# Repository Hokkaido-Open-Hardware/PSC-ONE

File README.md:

<p align="center">
  
</p>

# PSC-ONE SoC

[日本語・開発の目的](README_JP.md) · [Documentation](docs/README.md)

### Technical Specifications (PDF)

- **[PSC-ONE SoC Specification (Rev.0.9)](./docs/specs/PSC-ONE_SpecSheet.pdf)**  
  CPU, MMU, cache, SDRAM, NPU, peripherals, and SoC architecture.

- **[PSC-OS Specification (Rev.0.9)](./docs/specs/PSC_OS_Specs.pdf)**  
  OS architecture, boot process, system calls, ELF loader, FAT32, MicroPython, and TFLite runtime.

------------------------------------------------------------------------

An open-source full-stack RISC-V SoC platform for FPGA-based edge computing and AI acceleration.  
PSC-ONE integrates a custom CPU, memory subsystem, peripherals,
operating system, and AI accelerator into a unified architecture,
enabling end-to-end hardware/software co-design.

The PSC-NPU (SynapEngine) accelerator is controlled directly through custom
RISC-V CSR registers and accesses matrix data through the shared
cache/memory subsystem. This reduces explicit data transfers and
redundant memory copies during matrix operations and future neural-network workloads.

## Introduction Video

------------------------------------------------------------------------

## Contents

<!-- contents -->
- [What is PSC-ONE?](#what-is-psc-one)
- [PSC-ONE SoC Architecture](#psc-one-soc-architecture)
- [Repository Structure](#repository-structure)
- [Hardware Components](#hardware-components)
- [Software Stack](#software-stack)
- [CPU (PSC_RV32)](#cpu-psc_rv32)
- [CPU (PSC_RV32_V1)](#cpu-psc_rv32_v1)
- [CPU (PSC_RV32_V2)](#cpu-psc_rv32_v2)
- [CoreMark (CPU Core Only)](#coremark-cpu-core-only)
- [PSC-ONE AI](#psc-one-ai)
- [PSC-OS](#psc-os)
- [Demo](#demo)
- [PSC-ONE Speech Recognition Project](#psc-one-speech-recognition-project)
- [FST Viewer](#fst-viewer)
- [Development Status](#development-status)
- [Future Work](#future-work)
- [Getting Started](#getting-started)
- [Repository Status](#repository-status)
- [License](#license)
<!-- /contents -->

------------------------------------------------------------------------

The current PSC-ONE prototype hardware.\

The displayed color bars are generated directly by the PSC-ONE hardware and confirm correct operation of the LCD subsystem.

The PSC-ONE boot logo rendered on the actual FPGA hardware during system startup, demonstrating successful LCD initialization and graphics output.\

## What is PSC-ONE?

PSC-ONE is an open-source full-stack RISC-V SoC project developed by QPSC-Design.

It aims to build a fully custom edge computing platform from the ground up, including the following components:

- A custom RV32-based RISC-V CPU core
- A memory subsystem, including an SDRAM controller, caches, and an Sv32 MMU
- An SD card boot and storage interface
- Memory-mapped peripheral interfaces
- An AI acceleration engine, PSC-NPU, based on a systolic array architecture
- A custom operating system, PSC-OS

PSC-ONE is not just a CPU core, but a complete experimental SoC platform for research, edge AI development, and architectural exploration.

------------------------------------------------------------------------

## PSC-ONE SoC Architecture

This section presents the overall PSC-ONE SoC architecture, including the
PSC_RV32 CPU, memory subsystem, peripherals, PSC-OS, and PSC-ONE AI.

------------------------------------------------------------------------

## Repository Structure

| Directory | Contents |
| --- | --- |
| [hardware](hardware/README.md) | CPU/SoC RTL, bootloader and simulation |
| [software](software/os/OVERVIEW.md) | PSC-OS, MicroPython and applications |
| [board](board/README.md) | Board designs and prototype setup |
| [docs](docs/README.md) | Specifications, guides and validation records |
| [FST Viewer](tool/FST_viewer/README.md) | CPU waveform viewer |
| [IP](ip/README.md) | Project IP notes |

CPU v1 supports two PULP/CORE-V dot-product instructions. See the
[PULP specification](docs/cpu_pulp.md) ([日本語](docs/cpu_pulp_JP.md)).

------------------------------------------------------------------------

## Hardware Components

The hardware side of PSC-ONE currently includes:

- `PSC_RV32` custom RISC-V CPU core
- SDRAM controller
- SD card interface (SPI mode)
- Memory-mapped peripheral system
- PSC-NPU (SynapEngine) AI accelerator

------------------------------------------------------------------------

## Software Stack

The software side of PSC-ONE currently includes:

- `PSC-OS`, a custom operating system for the platform
- Boot and initialization flow for FPGA-based execution
- User programs and runtime experiments, including UART-based output demos

------------------------------------------------------------------------

## CPU (PSC_RV32)

### CPU Architecture

`cpu_legacy` is the CPU core developed during the initial prototyping phase of PSC-ONE.

See the [CPU guide](docs/cpu.md) and [hardware overview](hardware/README.md).

------------------------------------------------------------------------

## CPU (PSC_RV32_V1)

### CPU Architecture

> Diagram note: the drawing labels the main instruction FIFO as 32 words.
> The current v1 FetchUnit defaults to 16 words; the predicted-target FIFO
> remains 8 words. The image is retained as an earlier configuration.

See the [CPU guide](docs/cpu.md) and [hardware overview](hardware/README.md).

------------------------------------------------------------------------

## CPU (PSC_RV32_V2)

### Experimental Out-of-Order Architecture

`PSC_RV32_V2` is an experimental CPU with register renaming, a reorder buffer
(ROB), and an instruction queue (IQ). The current defaults are two ROB entries,
two IQ entries, and 34 physical registers. Independent ready instructions can
execute ahead of older stalled instructions; architectural state retires in
program order. These two in-flight slots do not imply two instructions retire
per clock. See the [hardware overview](hardware/README.md) for implementation links.

See the [CPU guide](docs/cpu.md) and [hardware overview](hardware/README.md).

------------------------------------------------------------------------

## CPU RV64 architecture

PSC_RV64 is an experimental 64-bit extension of the PSC_RV32 design.

targets RV64IM with Zicsr and Zifencei, extending the integer registers and
datapath to 64 bits while retaining 32-bit instruction encodings.

RV64 adds 64-bit load/store operations and word operations that produce
32-bit results sign-extended to 64 bits. The port also requires RV64-specific
handling of shift amounts, arithmetic, multiplication and division.

Initial development focuses on bare-metal execution and adapting the existing
C/C++ test programs using `-march=rv64im_zicsr_zifencei -mabi=lp64`.
Sv39 virtual memory and PSC-OS support are separate development steps;
64-bit execution alone does not establish Linux compatibility.

The core remains experimental. RV32 regression results and CoreMark scores
do not establish RV64 correctness or performance; RV64 validation results
will be documented separately.

------------------------------------------------------------------------

## CoreMark (CPU Core Only)

CoreMark was also measured with the SDRAM/cache path removed and replaced by a 1-cycle cocotb memory model.
This isolates the CPU core from SDRAM wait states, cache misses, and refill latency.

```text
CPU       CoreMark    CoreMark/MHz    Execution Time    CRC Validation
-----------------------------------------------------------------------
cpu_v1    80.879974   0.808800        12.364 s          PASS
cpu_v2    53.287861   0.532879        18.766 s          PASS
```

Recorded measurement conditions (historical results, not rerun for this documentation update):

- 100 MHz
- GCC 14.2.0
- The original table states 500 iterations for both CPUs; this is inconsistent with the v1 score/time pair (see note below).
- 1-cycle memory response
- No SDRAM wait states
- No cache-miss or refill penalty
- Identical CoreMark binary for `cpu_v1` and `cpu_v2`
- CRC Validation: PASS

These are CPU-core-only measurements under a 1-cycle memory model.
The v1 score × execution time is approximately 1,000, whereas v2 gives 500.
The original v1 iteration count or score/time entry therefore needs confirmation
from its measurement log. Values are retained as recorded, not silently corrected.
See [CoreMark reproduction and interpretation](hardware/sim/coremark_psc/README.md).

------------------------------------------------------------------------

## PSC-ONE AI

PSC-ONE AI is a hardware accelerator platform for matrix multiplication (GEMM),
built around a custom systolic-array architecture.

It is part of the broader PSC-ONE experimental SoC platform,
which integrates:

- Custom RISC-V CPU
- Memory subsystem
- AI accelerator
- Hardware/software co-design environment

The project focuses on exploring efficient dataflow architectures
under constrained memory bandwidth for edge AI systems.

------------------------------------------------------------------------

### PSC-ONE AI Architecture

> Diagram note: “share a single multiplier” describes the shared-arithmetic
> concept. The legacy multiplier count is configurable; NPU v1 uses four
> physical multiplier lanes. The drawing is not an exact v1/v2 netlist.

The system integrates the PSC-NPU systolic array
with the PSC-ONE SoC platform.

------------------------------------------------------------------------

### PSC-ONE AI Features

- 4×4 INT8 systolic array
- Output-Stationary (OS) dataflow
- Direct control through custom RISC-V CSR registers
- Direct matrix data access through the CPU cache/memory subsystem
- Integrated with the custom PSC-RV32 processor
- Experimental hardware/software co-design platform

------------------------------------------------------------------------

### 8×8 Matrix Multiplication Performance

The following historical results compare the execution time of an 8×8 matrix multiplication across different PSC-RV32 configurations and the systolic array accelerator.

#### Execution Time Comparison

| Configuration                                  | Execution Time | Performance vs. V1 |
| ---------------------------------------------- | -------------: | -----------------: |
| PSC_RV32                                       |         591 µs |       ~1.80× faster |
| PSC_RV32_V1                                    |        1066 µs |           Baseline |
| Systolic Array                                 |          44 µs |       ~24.2× faster |
| PSC_RV32_V1 (Fetch FIFO enabled)               |         742 µs |       ~1.44× faster |
| PSC_RV32_V1 (R/I-Type pipeline enabled)        |         651 µs |       ~1.64× faster |

#### Results

The systolic array completed the 8×8 matrix multiplication in **44 µs**, approximately **24.2× faster** than the baseline PSC_RV32_V1 processor.

Enabling the Fetch FIFO reduced the PSC_RV32_V1 execution time from **1066 µs to 742 µs**. Enabling the R/I-Type pipeline further reduced it to **651 µs**, approaching the performance of the original PSC_RV32 processor at **591 µs**.

These results demonstrate that both instruction-fetch optimization and R/I-Type pipelining significantly improve CPU performance. However, the dedicated systolic array still provides a much larger performance advantage for matrix multiplication workloads.

------------------------------------------------------------------------

### PSC-NPU and PicoRV32 Resource Scale Comparison

PicoRV32 is an archived generic-cell result; its MUX count is corrected to 100
from the saved log. FF-family counts are register cells, not individual bits.
See the [CPU comparison and provenance](docs/cpu.md#psc_rv32-vs-picorv32-yosys-analysis).

#### Resource Comparison

This is a historical generic Yosys cell comparison for the legacy NPU, not
FPGA LUT/FF usage or the current NPU v1 resource count. NPU v1 has four physical
multiplier lanes; see [its implementation](hardware/rtl/soc/npu_v1/README.md).

| Metric         | PSC-NPU (4×4)        | PicoRV32 |
| -------------- | -------------------: | -------: |
| Cells          |                  555 |      515 |
| Multipliers    |                **2** |    **0** |
| Adders         |                   25 |        8 |
| Multiplexers   |                  113 |      100 |
| FF-family cells |                   88 |      105 |
| Control Logic  |             Moderate |     High |

> Multiplexer counts include Yosys `$mux` cells only and exclude `$pmux` cells.

- A **dataflow-oriented compute engine (Systolic Array)**
- A **control-oriented general-purpose CPU (PicoRV32)**

------------------------------------------------------------------------

## PSC-OS

[OS architecture and boot](docs/psc_os.md) · [API reference](docs/psc_os_api.md) · [MMU](docs/cpu_mmu.md)

PSC-OS is a custom operating system developed specifically for the PSC-ONE platform.

Unlike Linux, BSD, or existing RTOSes, PSC-OS is designed together with the PSC_RV32 CPU, memory subsystem, peripherals, and hardware accelerators, providing a tightly integrated hardware/software co-design environment.

The following diagram illustrates the software architecture of PSC-OS, including user applications, the kernel, device drivers, and the underlying PSC-ONE hardware platform.

> Diagram note: FAT32 is drawn inside the kernel, but the current shell/ELF path
> links FAT32 into the user image and accesses SD hardware through system calls.
> The image is retained as a conceptual overview, not a privilege-boundary map.

> This diagram presents the conceptual architecture of PSC-OS and PSC-ONE. Some modules shown may represent planned or experimental extensions.

Current PSC-OS features include:

- Bootloader and kernel
- Machine, Supervisor, and User privilege modes
- Sv32 virtual memory
- ECALL-based system-call interface
- Interactive command shell
- FAT32 filesystem support
- SD-card boot and storage
- User-program loading and execution
- Device drivers for UART, LCD, I2S microphone, and SD card
- PSC-NPU software support; PFE OS API integration remains future work

PSC-OS serves both as the runtime environment for the PSC-ONE SoC and as an experimental platform for operating-system, CPU, and hardware/software co-design research.

------------------------------------------------------------------------

### ELF Loader

PSC-OS includes an ELF loader for running RISC-V user programs from the SD card. The loader reads an ELF executable through the FAT32 filesystem, places its loadable segments in memory, and starts execution at the entry point specified by the file.
This allows user applications to be built as ELF executables instead of being converted to raw memory images. It also provides a foundation for expanding PSC-OS’s user-program support.

Example of running the sample `HELLO.ELF` from the PSC-OS shell:

```text
PSC_OS> run HELLO.ELF
ELF: entry=00400000 sp=00500000 pages=3
Hello from user ELF!
run: exit 0
PSC_OS>
```

------------------------------------------------------------------------

### MicroPython on PSC-OS

MicroPython has been ported to PSC-OS and can run as a user-space application on the custom PSC_RV32 CPU.
The following console output is an excerpt from an actual execution on PSC-ONE.

```text
PSC_OS Boot Start.........
--- memset done ---
Test Ver: test_1.5.0

+--------------------------------------------------+
|                    PSC_OS                        |
|            Minimal RISC-V Kernel Boot            |
+--------------------------------------------------+
| CPU   : RV32 (Supervisor mode)
| MMU   : SV32
| UART  : SBI console or
| UART  : MMIO console
| CMD   : hello, primes, dump
| CMD   : sa_start
| CMD   : sd_read, sd_write
| CMD   : mic_read, mic_write
| CMD   : fat32_info, fat32_ls, fat32_cat
| CMD   : fat32_touch
| CMD   : speech
+--------------------------------------------------+
...
MicroPython v1.29.0-preview.727.g7de32aa1ae on 2026-08-18; minimal with unknown-cpu

>>> a = 10
>>> a * 20
200

>>> p = [n for n in range(10)]
>>> print(p)
[0, 1, 2, 3, 4, 5, 6, 7, 8, 9]

>>> print(sum(p))
45

>>> print(sum(((i%1000)*(i%1000)//((i%97)+1) for i in range(1,5000))))
88859578

>>> import math
>>> print(sum(math.sin(i) for i in range(100)))
0.37919468

>>> [print(" "*int(20+15*math.sin(i/4))+"*") for i in range(40)]
                    *
                       *
                           *
                              *
                                *
                                  *
                                  *
                                 *
                               *
                            *
                         *
                      *
                  *
              *
           *
        *
      *
     *
       *
         *
            *
               *
                   *
                       *
                          *
                             *
                                *
                                  *
                                 *
                               *
                             *
                          *
                      *
                  *
               *

>>> import psc

>>> psc.run("TEST1.PY")

Hello from SD card

10

20

2000

>>> psc.run("TEST2.PY")

=== PSC-ONE MicroPython SD Test ===

1 sin= 0.32719472 cos= 0.9800666 mix= 0.32067264

2 sin= 0.6183698 cos= 0.921061 mix= 0.5695563

3 sin= 0.841471 cos= 0.8253356 mix= 0.694496

4 sin= 0.9719379 cos= 0.6967067 mix= 0.6771557

5 sin= 0.99540792 cos= 0.5403023 mix= 0.5378212

```

This demonstrates that the PSC-ONE software stack can execute an interactive Python environment directly on the custom RISC-V processor, including integer arithmetic, list comprehensions, generators, and floating-point math functions provided by MicroPython.

------------------------------------------------------------------------

### Thonny on MicroPython

Thonny provides a graphical development environment for working with MicroPython on PSC-OS. It connects to PSC-ONE through a USB-to-UART interface, allowing Python code to be edited on the PC and sent to the board for execution.

The integration uses MicroPython’s raw REPL protocol to transfer code and return execution results. The code runs on the custom PSC_RV32 CPU, while Thonny displays program output and error messages on the PC.

With the PSC-OS Thonny support in place, the basic workflow is:

1. Start MicroPython from the PSC-OS shell using the `microPython` command.
2. Close the serial terminal to release the UART port.
3. Select **MicroPython (generic)** in Thonny and choose the serial port connected to PSC-ONE.
4. Write a Python script in the editor and run it on the board.

Scripts can be transferred and executed directly in RAM without first saving them to the SD card. Access to PSC-ONE-specific functions is provided through the `psc` module.

This integration brings the existing MicroPython environment into a desktop editor, making it easier to develop and test Python programs for PSC-ONE.

------------------------------------------------------------------------

## Demo

### PSC-OS LCD Demo

This video shows a live demonstration of the PSC system running on FPGA hardware.\
It highlights real-time interaction between the CPU, SD card interface, and UART output.\
The system successfully boots and executes software on a fully integrated hardware platform.

------------------------------------------------------------------------

## PSC-ONE Speech Recognition Project

### Background

This speech-recognition project started from PSC-ONE.

In June 2026, I wrote **"PSC-ONEによる音声認識①（キックオフ編）"**.

About two months have passed since then.

The project has finally reached an important milestone, so the current
results are summarized here.

### Image

The PC is connected to the PSC-ONE board via UART.
Speech recognition is performed by speaking into the microphone connected to PSC-ONE,
while the recognition results are displayed on the PC through the UART console.\

### Equipment

-   PSC-ONE FPGA platform
-   Custom PSC_RV32 RISC-V CPU
-   PSC-OS
-   I2S microphone
-   PSC-NPU (SynapEngine) AI accelerator

### Results

The following output is from an actual speech-recognition test running
on PSC-ONE.

#### UP

``` text
PSC_OS> speech
Speech recognition start

（私の声でアップ）

SPEECH RECORD START samples=48000
SPEECH RECORD END samples=48000
VOICE RANGE start=0 end=32000
SCORE UP=22776 DOWN=-71191 UNKNOWN=-14509
SPEECH RESULT=UP
RESULT: UP
```

#### DOWN

``` text
PSC_OS> speech
Speech recognition start

（私の声でダウン）

SPEECH RECORD START samples=48000
SPEECH RECORD END samples=48000
VOICE RANGE start=0 end=32000
SCORE UP=-85630 DOWN=5339 UNKNOWN=-9757
SPEECH RESULT=DOWN
```

In the current implementation, speech recognition succeeds approximately
**70% of the time**.

This marks the completion of the first working PSC-ONE
speech-recognition implementation.

------------------------------------------------------------------------

## PSC-ONE YOLOv8n Demo Project

This project demonstrates YOLOv8n object detection on **PSC-ONE**, a custom FPGA-based RISC-V SoC.

JPEG images and a TFLite model are loaded from an SD card. PSC-OS handles image preprocessing, inference, and detection postprocessing. The project explores running neural-network inference on a small FPGA system using a variety of test images.

### System Configuration

- **Hardware:** Tang Nano 20K / PSC-ONE
- **CPU:** Custom RISC-V CPU
- **OS:** PSC-OS
- **Model:** YOLOv8n, INT8-quantized TFLite model (approximately 3.5 MB)
- **Model input resolution:** 160 × 160 pixels
- **Image source:** JPEG files stored on an SD card

### Input Images and Detection Results

| Sample | Input Image | Detection Result |
| :--- | :---: | :---: |
| ANIME |  |  |
| BUS |  |  |
| CUPBAN |  |  |
| NEKO |  |  |
| DOG |  |  |

This demo focuses on validating inference in an embedded environment rather than achieving real-time performance. Detection results depend on the input image and the object classes supported by the pretrained model.

------------------------------------------------------------------------

## FST Viewer

PSC-ONE includes **FST Viewer (PSC_RV32 Trace Studio)**, a Python-based browser GUI for visualizing CPU execution traces generated by simulation.

The viewer reads FST/VCD waveform files and presents CPU activity at the instruction and architectural level rather than displaying only raw RTL signals. It is designed specifically for the PSC_RV32 processor family and does not require any modification to the RTL.

Currently supported CPU architectures are:

- `PSC_RV32` (legacy FSM architecture)
- `PSC_RV32_V1` (valid/ready pipeline architecture)
- `PSC_RV32_V2` (experimental out-of-order architecture)

The CPU architecture is automatically detected from the trace structure.

FST Viewer provides:

- Instruction-level execution timeline
- CPU pipeline and execution-stage visualization
- Instruction tracking across multiple cycles
- PC and instruction search
- Instruction filtering
- Instruction Ledger with PC, instruction word, disassembly, execution cycles, and retire status
- Cycle Inspector for register operands, execution results, memory accesses, hazards, and CPU state
- Architectural register display (`x0`–`x31`) with ABI names and value-change highlighting
- MUL/DIV execution and wait-state visualization
- Support for legacy, V1, and experimental V2 CPU architectures

The horizontal axis represents CPU clock cycles, allowing execution behavior to be inspected cycle by cycle.

For example, the viewer can show how an instruction moves through the CPU, how long it remains in each execution stage, when register values change, and where pipeline stalls or long-latency MUL/DIV operations occur.

The viewer runs locally using Python and a standard JavaScript/Canvas-capable web browser.

```bash
cd PSC-ONE/tool/FST_viewer
python3 fst_viewer.py
```

When no trace file is specified, the viewer automatically selects the latest FST/VCD file generated in:

```text
hardware/sim/wave/
```

A specific trace can also be opened directly:

```bash
python3 fst_viewer.py trace.fst
```

The default web interface runs on `127.0.0.1:8000`. If the port is already in use, the viewer automatically searches for the next available port.

FST Viewer is intended to make PSC_RV32 CPU development and verification easier by providing a higher-level view of processor execution than conventional waveform inspection alone.

------------------------------------------------------------------------

## Development Status

### Hardware

#### CPU
- [x] RV32I Base Integer Instruction Set
- [x] RV32M Multiply/Divide Extension
- [x] Zicsr and Zifencei Extensions
- [x] Selected PULP SIMD instructions (`cv.dotup.h`, `cv.dotsp.b`)
- [ ] Full Pipeline Execution
- [x] Partial Pipeline Execution for selected instruction types
- [x] Branch Instructions
- [x] Load / Store Instructions
- [x] CSR Support
- [x] ECALL / SRET Support
- [x] MMU (Sv32)
- [x] Interrupt Controller

#### Memory System
- [x] SDRAM Controller
- [x] AXI4 Memory Interface
- [x] Cache Controller
- [x] Virtual Memory Support
- [x] DMA Engine

#### AI Accelerator
- [x] PSC-NPU Architecture
- [x] 4×4 INT8 Systolic Array
- [x] Matrix Multiplication API
- [x] Shared Memory Integration
- [ ] Larger Systolic Array
- [ ] Quantized Neural Network Inference

#### Peripherals
- [x] UART
- [x] LED Controller
- [x] Timer
- [x] SD Card (SPI Mode, Read)
- [x] SD Card (SPI Mode, Write)
- [x] LCD Controller
- [ ] Ethernet
- [ ] USB

### Software

#### PSC-OS
- [x] Bootloader
- [x] FAT32 Bootloader
- [x] Kernel
- [x] User Mode Execution
- [x] System Call Interface
- [x] Command Shell
- [x] Memory Management
- [x] SD Card Driver
- [x] SD Card Program Loader
- [x] FAT32 File System
- [x] ELF Loader
- [ ] Networking Stack

#### Device Drivers
- [x] UART
- [x] Timer
- [x] SDRAM Controller
- [x] LCD Controller (ILI9488)
- [x] I2S Microphone Interface
- [x] Systolic Array Accelerator

#### Applications
- [x] Prime Number Benchmark
- [x] Matrix Multiplication Demo
- [x] SDRAM Test
- [x] SD Card Test
- [x] FAT32 File Browser (`ls`, `cat`)
- [x] FAT32 File Write
- [x] JPEG Image Viewer (jpeg) — 480×320 LCD Display
- [x] AI Inference Demo
- [x] Audio Processing Demo
- [x] Speech Recognition Demo

### Verification

#### Simulation
- [x] Icarus Verilog
- [x] Verilator
- [x] Cocotb Test Environment
- [x] Official RISC-V ISA tests: 49 RV32I/RV32M tests passed
- [x] SDRAM Tests
- [x] MMU Tests
- [x] PSC-OS Boot Test

#### FPGA
- [x] Tang 20K
- [x] SDRAM Boot
- [x] PSC-OS Boot
- [x] UART Console
- [x] SD Card Boot
- [x] PSC-NPU Execution
- [ ] Long-Term Stability Test

### Documentation

- [x] Project Overview
- [x] Build Instructions
- [x] Simulation Guide
- [x] Hardware Architecture
- [ ] Software Architecture
- [ ] Developer Guide
- [x] API Reference

### Future Goals

- [ ] PSC-ONE v1.0 Release
- [ ] Neural Network Inference on PSC-NPU
- [ ] Extend the existing speech-recognition demo
- [ ] Self-Balancing Robot Demo
- [ ] Custom ASIC Prototype

------------------------------------------------------------------------

## Future Work

### Demonstration Robot

A demonstration of a two-wheeled self-balancing robot controlled by the PSC-ONE board is also planned

### PFE

#### PSC-ONE Phase Flow Engine

The PSC-ONE Phase Flow Engine is an experimental hardware accelerator architecture developed as part of the PSC project.
It is designed for future AI, signal-processing, and data-flow computing research on the PSC-ONE platform.

Location:

```text
hardware/rtl/soc/pfe/
```

------------------------------------------------------------------------

## Getting Started

Commands below start at the repository root (the directory containing `PSC-ONE/`).
With the RISC-V toolchain, Verilator and a Python environment containing cocotb:

```sh
cd PSC-ONE/hardware/sim
make -f Makefile.riscv.sim simulate_RISCV_TESTS_PARALLEL CPU_VERSION=v1
make -f Makefile.cpu.core simulate_CPU_CORE CPU_VERSION=v1
make -f Makefile.pscos simulate_PSCOS CPU_VERSION=v1
```

OS simulation can take a long time. See the [software guide](software/os/OVERVIEW.md)
and [board setup](board/PSC-ONE/README.md) for the next steps.

At a high level, the workflow is as follows:

1. Build the hardware design
2. Program the FPGA
3. Prepare the boot image or software binaries
4. Run the system and observe output through the available interfaces

For detailed instructions, see the [Getting Started Guide](docs/getting-started.md).

------------------------------------------------------------------------

## Repository Status

This repository is an experimental research project
and is under active development.

RTL, software, and architecture may change frequently.

------------------------------------------------------------------------

## License

MIT License

------------------------------------------------------------------------

### Work in Progress

This project is actively under development.\
Features, architecture, interfaces, and documentation may change as the design evolves.

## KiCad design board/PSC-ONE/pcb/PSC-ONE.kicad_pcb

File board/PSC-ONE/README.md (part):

# PSC-ONE Design

[PSC-ONE](../../README.md) · [Documentation](../../docs/README.md)

The current PSC-ONE prototype hardware.\

<!-- contents -->
- [Purpose](#purpose)
- [Features](#features)
- [Getting Started](#getting-started)
- [License](#license)
<!-- /contents -->

## Purpose

PSC-ONE is a hardware evaluation and demonstration platform for the PSC project.

The board is designed to verify and validate the functionality of the PSC CPU, operating system, memory subsystem, peripherals, and AI acceleration technologies in a real hardware environment.

It also serves as a demonstration platform for various embedded applications, including:

- Voice recognition
- AI inference
- Graphics and display control
- Sensor integration
- Real-time embedded systems

## Features

- Custom PSC RISC-V CPU
- PSC-OS operating system support
- SDRAM memory interface
- LCD display interface
- Optional touch panel support
- SD card storage interface
- UART debugging console
- GPIO expansion
- AI accelerator integration support

## Getting Started

### Program the FPGA

Build the FPGA bitstream and program the PSC-ONE board using the Gowin Programmer.

After successful programming, connect:

* UART console
* SD card containing PSC-OS images
* LCD module (optional)

### Prepare the SD Card

Match the SD layout to the bootloader in the FPGA image. Two flows exist:

| Bootloader | SD layout |
| --- | --- |
| [FAT32 loader](../../software/os/src/boot/bootloader_fat32.c) | `KERNEL.MEM` and `USER.MEM` in the FAT32 root |
| [Legacy raw-image writer](../../hardware/bootloader/Makefile) | `kernel.img` at sector 100, `user.img` at sector 300 |

The raw-image writer currently hard-codes `/dev/sdc`; it does not accept a
`/dev/sdX` placeholder or automatically select a card. Inspect the actual device
and the selected bootloader before using that writer. The historical log below
belongs to the earlier raw-sector flow and is not a current layout specification.

Build the FAT32 bootloader from the repository root with the OS Makefile's
`fpga_fat32_boot` target (see that [Makefile](../../software/os/Makefile) for
available build targets and outputs).

### Boot PSC-OS

1. Insert the SD card into PSC-ONE.
2. Power on the board.
3. Open the UART console.

The bootloader loads:

1. `kernel.img` from the SD card into SDRAM
2. `user.img` from the SD card into SDRAM
3. Transfers control to PSC-OS

Historical boot log (June 2026; addresses and image sizes are build-dependent):

<details>
<summary>Show the full recorded boot log</summary>

```text
boot start

=== PSC random memory RW test start ===
[mem_check] range 00400000 - 00800000
[mem_check] access count=00000064
[mem_check] OK

=== PSC bootloader start ===
CTRL=0000000A
SD INIT start
LOAD: LBA=00000064 count=00000024 -> addr=00200000
RD[00000000] = 00256537
RD[00000004] = B1450513
RD[00000008] = 00050113
RD[0000000C] = 5000106F
RD[00000010] = 100005B7
RD[00000014] = 0085A603
RD[00000018] = 00167613
RD[0000001C] = 00060663
RD[00000020] = 00000013
RD[00000024] = FF1FF06F
RD[00000028] = 00A5A023
RD[0000002C] = 00008067
RD[00000030] = 100005B7
RD[00000034] = 0085A603
RD[00000038] = 00167613
RD[0000003C] = 00060663
WR[00000000] = 00256537
WR[00000004] = B1450513
WR[00000008] = 00050113
WR[0000000C] = 5000106F
WR[00000010] = 100005B7
WR[00000014] = 0085A603
WR[00000018] = 00167613
WR[0000001C] = 00060663
WR[00000020] = 00000013
WR[00000024] = FF1FF06F
WR[00000028] = 00A5A023
WR[0000002C] = 00008067
WR[00000030] = 100005B7
WR[00000034] = 0085A603
WR[00000038] = 00167613
WR[0000003C] = 00060663
  loaded sector 00000000 / 00000024
RD[00000000] = 04412883
RD[00000004] = 04812403
RD[00000008] = 04C12483
RD[0000000C] = 05012903
RD[00000010] = 05412983
RD[00000014] = 05812A03
RD[00000018] = 05C12A83
RD[0000001C] = 06012B03
RD[00000020] = 06412B83
RD[00000024] = 06812C03
RD[00000028] = 06C12C83
RD[0000002C] = 07012D03
RD[00000030] = 07412D83
RD[00000034] = 07812103
RD[00000038] = 10200073
RD[0000003C] = FCC10113
WR[00000000] = 04412883
WR[00000004] = 04812403
WR[00000008] = 04C12483
WR[0000000C] = 05012903
WR[00000010] = 05412983
WR[00000014] = 05812A03
WR[00000018] = 05C12A83
WR[0000001C] = 06012B03
WR[00000020] = 06412B83
WR[00000024] = 06812C03
WR[00000028] = 06C12C83
WR[0000002C] = 07012D03
WR[00000030] = 07412D83
WR[00000034] = 07812103
WR[00000038] = 10200073
WR[0000003C] = FCC10113
RD[00000000] = 00001637
RD[00000004] = FFC60613
RD[00000008] = 00C47633
RD[0000000C] = 00C56533
RD[00000010] = 00B52023
RD[00000014] = 01C12083
RD[00000018] = 01812403
RD[0000001C] = 01412483
RD[00000020] = 01012903
RD[00000024] = 00C12983
RD[00000028] = 00812A03
RD[0000002C] = 02010113
RD[00000030] = 00008067
RD[00000034] = 00000013
RD[00000038] = FFDFF06F
RD[0000003C] = FC010113
WR[00000000] = 00001637
WR[00000004] = FFC60613
WR[00000008] = 00C47633
WR[0000000C] = 00C56533
WR[00000010] = 00B52023
WR[00000014] = 01C12083
WR[00000018] = 01812403
WR[0000001C] = 01412483
WR[00000020] = 01012903
WR[00000024] = 00C12983
WR[00000028] = 00812A03
WR[0000002C] = 02010113
WR[00000030] = 00008067
WR[00000034] = 00000013
WR[00000038] = FFDFF06F
WR[0000003C] = FC010113
RD[00000000] = 00356637
RD[00000004] = 00060493
RD[00000008] = 70A5A623
RD[0000000C] = 02A4F263
RD[00000010] = 00203537
RD[00000014] = 10C50513
RD[00000018] = 002035B7
RD[0000001C] = D2658593
RD[00000020] = 08900613
RD[00000024] = 00001097
RD[00000028] = 18C080E7
RD[0000002C] = 0000006F
RD[00000030] = 00001637
RD[00000034] = 00001437
RD[00000038] = 00090513
RD[0000003C] = 00000593
WR[00000000] = 00356637
WR[00000004] = 00060493
WR[00000008] = 70A5A623
WR[0000000C] = 02A4F263
WR[00000010] = 00203537
WR[00000014] = 10C50513
WR[00000018] = 002035B7
WR[0000001C] = D2658593
WR[00000020] = 08900613
WR[00000024] = 00001097
WR[00000028] = 18C080E7
WR[0000002C] = 0000006F
WR[00000030] = 00001637
WR[00000034] = 00001437
WR[00000038] = 00090513
WR[0000003C] = 00000593
RD[00000000] = E4C50513
RD[00000004] = 00001097
RD[00000008] = FAC080E7
RD[0000000C] = 00092503
RD[00000010] = 00157593
RD[00000014] = 08059663
RD[00000018] = 00225537
RD[0000001C] = 70854583
RD[00000020] = 00058863
RD[00000024] = 00225537
RD[00000028] = 70C52983
RD[0000002C] = 0140006F
RD[00000030] = 00100593
RD[00000034] = 70B50423
RD[00000038] = 00256537
RD[0000003C] = 00050993
WR[00000000] = E4C50513
WR[00000004] = 00001097
WR[00000008] = FAC080E7
WR[0000000C] = 00092503
WR[00000010] = 00157593
WR[00000014] = 08059663
WR[00000018] = 00225537
WR[0000001C] = 70854583
WR[00000020] = 00058863
WR[00000024] = 00225537
WR[00000028] = 70C52983
WR[0000002C] = 0140006F
WR[00000030] = 00100593
WR[00000034] = 70B50423
WR[00000038] = 00256537
WR[0000003C] = 00050993
RD[00000000] = 00000593
RD[00000004] = 00001097
RD[00000008] = C90080E7
RD[0000000C] = 00C9D513
RD[00000010] = 00A51513
RD[00000014] = 00150513
RD[00000018] = 10A92023
RD[0000001C] = 00A55513
RD[00000020] = 00C51513
RD[00000024] = 040025B7
RD[00000028] = 80758593
RD[0000002C] = 00B52C23
RD[00000030] = 180A8463
RD[00000034] = 180B0263
RD[00000038] = 00203537
RD[0000003C] = DEA50513
WR[00000000] = 00000593
WR[00000004] = 00001097
WR[00000008] = C90080E7
WR[0000000C] = 00C9D513
WR[00000010] = 00A51513
WR[00000014] = 00150513
WR[00000018] = 10A92023
WR[0000001C] = 00A55513
WR[00000020] = 00C51513
WR[00000024] = 040025B7
WR[00000028] = 80758593
WR[0000002C] = 00B52C23
WR[00000030] = 180A8463
WR[00000034] = 180B0263
WR[00000038] = 00203537
WR[0000003C] = DEA50513
RD[00000000] = 03812403
RD[00000004] = 03412483
RD[00000008] = 03012903
RD[0000000C] = 02C12983
RD[00000010] = 02812A03
RD[00000014] = 02412A83
RD[00000018] = 02012B03
RD[0000001C] = 01C12B83
RD[00000020] = 01812C03
RD[00000024] = 01412C83
RD[00000028] = 01012D03
RD[0000002C] = 00C12D83
RD[00000030] = 04010113
RD[00000034] = 00008067
RD[00000038] = 00203537
RD[0000003C] = 10C50513
WR[00000000] = 03812403
WR[00000004] = 03412483
WR[00000008] = 03012903
WR[0000000C] = 02C12983
WR[00000010] = 02812A03
WR[00000014] = 02412A83
WR[00000018] = 02012B03
WR[0000001C] = 01C12B83
WR[00000020] = 01812C03
WR[00000024] = 01412C83
WR[00000028] = 01012D03
WR[0000002C] = 00C12D83
WR[00000030] = 04010113
WR[00000034] = 00008067
WR[00000038] = 00203537
WR[0000003C] = 10C50513
RD[00000000] = 00660693
RD[00000004] = 41F6D713
RD[00000008] = 01D75713
RD[0000000C] = 00E68733
RD[00000010] = FF877713
RD[00000014] = 40E686B3
RD[00000018] = 00469713
RD[0000001C] = 00D69693
RD[00000020] = 00E686B3
RD[00000024] = 00225737
RD[00000028] = 73070713
RD[0000002C] = 00D706B3
RD[00000030] = 0046A803
RD[00000034] = 00100793
RD[00000038] = 00F81663
RD[0000003C] = 0006A803
WR[00000000] = 00660693
WR[00000004] = 41F6D713
WR[00000008] = 01D75713
WR[0000000C] = 00E68733
WR[00000010] = FF877713
WR[00000014] = 40E686B3
WR[00000018] = 00469713
WR[0000001C] = 00D69693
WR[00000020] = 00E686B3
WR[00000024] = 00225737
WR[00000028] = 73070713
WR[0000002C] = 00D706B3
WR[00000030] = 0046A803
WR[00000034] = 00100793
WR[00000038] = 00F81663
WR[0000003C] = 0006A803
RD[00000000] = 03854603
RD[00000004] = 01881813
RD[00000008] = 00F86533
RD[0000000C] = 00D566B3
RD[00000010] = 00070513
RD[00000014] = 00C12083
RD[00000018] = 01010113
RD[0000001C] = 00001317
RD[00000020] = 00830067
RD[00000024] = 00203537
RD[00000028] = 08E50513
RD[0000002C] = 002035B7
RD[00000030] = D2658593
RD[00000034] = 29100613
RD[00000038] = 00000097
RD[0000003C] = 778080E7
WR[00000000] = 03854603
WR[00000004] = 01881813
WR[00000008] = 00F86533
WR[0000000C] = 00D566B3
WR[00000010] = 00070513
WR[00000014] = 00C12083
WR[00000018] = 01010113
WR[0000001C] = 00001317
WR[00000020] = 00830067
WR[00000024] = 00203537
WR[00000028] = 08E50513
WR[0000002C] = 002035B7
WR[00000030] = D2658593
WR[00000034] = 29100613
WR[00000038] = 00000097
WR[0000003C] = 778080E7
  loaded sector 00000008 / 00000024
RD[00000000] = 03212023
RD[00000004] = 01312E23
RD[00000008] = 01412C23
RD[0000000C] = 01512A23
RD[00000010] = 01612823
RD[00000014] = 01712623
RD[00000018] = 01812423
RD[0000001C] = 00058613
RD[00000020] = 00050413
RD[00000024] = 40A58A33
RD[00000028] = 002A5493
RD[0000002C] = 00203537
RD[00000030] = 2C450513
RD[00000034] = 00040593
RD[00000038] = 00000097
RD[0000003C] = 578080E7
WR[00000000] = 03212023
WR[00000004] = 01312E23
WR[00000008] = 01412C23
WR[0000000C] = 01512A23
WR[00000010] = 01612823
WR[00000014] = 01712623
WR[00000018] = 01812423
WR[0000001C] = 00058613
WR[00000020] = 00050413
WR[00000024] = 40A58A33
WR[00000028] = 002A5493
WR[0000002C] = 00203537
WR[00000030] = 2C450513
WR[00000034] = 00040593
WR[00000038] = 00000097
WR[0000003C] = 578080E7
RD[00000000] = 00A40533
RD[00000004] = 00040593
RD[00000008] = 0125C633
RD[0000000C] = 00C5A023
RD[00000010] = 00458593
RD[00000014] = FEA59AE3
RD[00000018] = 00203537
RD[0000001C] = C5250513
RD[00000020] = 00000097
RD[00000024] = 390080E7
RD[00000028] = 00400513
RD[0000002C] = 08A9EE63
RD[00000030] = 00000993
RD[00000034] = 40900533
RD[00000038] = 0024B593
RD[0000003C] = 40B005B3
WR[00000000] = 00A40533
WR[00000004] = 00040593
WR[00000008] = 0125C633
WR[0000000C] = 00C5A023
WR[00000010] = 00458593
WR[00000014] = FEA59AE3
WR[00000018] = 00203537
WR[0000001C] = C5250513
WR[00000020] = 00000097
WR[00000024] = 390080E7
WR[00000028] = 00400513
WR[0000002C] = 08A9EE63
WR[00000030] = 00000993
WR[00000034] = 40900533
WR[00000038] = 0024B593
WR[0000003C] = 40B005B3
RD[00000000] = 00000097
RD[00000004] = 1B0080E7
RD[00000008] = 00203537
RD[0000000C] = 37350513
RD[00000010] = 002255B7
RD[00000014] = 70358593
RD[00000018] = 40A585B3
RD[0000001C] = FFFFF097
RD[00000020] = E20080E7
RD[00000024] = 00203537
RD[00000028] = C8E50513
RD[0000002C] = 00000097
RD[00000030] = 184080E7
RD[00000034] = FFFFF097
RD[00000038] = 624080E7
RD[0000003C] = 00203537
WR[00000000] = 00000097
WR[00000004] = 1B0080E7
WR[00000008] = 00203537
WR[0000000C] = 37350513
WR[00000010] = 002255B7
WR[00000014] = 70358593
WR[00000018] = 40A585B3
WR[0000001C] = FFFFF097
WR[00000020] = E20080E7
WR[00000024] = 00203537
WR[00000028] = C8E50513
WR[0000002C] = 00000097
WR[00000030] = 184080E7
WR[00000034] = FFFFF097
WR[00000038] = 624080E7
WR[0000003C] = 00203537
RD[00000000] = 04C12C23
RD[00000004] = 04B12A23
RD[00000008] = 05410513
RD[0000000C] = 00A12C23
RD[00000010] = 02500913
RD[00000014] = 07200993
RD[00000018] = 06400493
RD[0000001C] = 00D10A93
RD[00000020] = 00900B13
RD[00000024] = 00100B93
RD[00000028] = 07300C13
RD[0000002C] = 07800C93
RD[00000030] = 00203537
RD[00000034] = 31D50D13
RD[00000038] = 00C0006F
RD[0000003C] = 20050263
WR[00000000] = 04C12C23
WR[00000004] = 04B12A23
WR[00000008] = 05410513
WR[0000000C] = 00A12C23
WR[00000010] = 02500913
WR[00000014] = 07200993
WR[00000018] = 06400493
WR[0000001C] = 00D10A93
WR[00000020] = 00900B13
WR[00000024] = 00100B93
WR[00000028] = 07300C13
WR[0000002C] = 07800C93
WR[00000030] = 00203537
WR[00000034] = 31D50D13
WR[00000038] = 00C0006F
WR[0000003C] = 20050263
RD[00000000] = 060080E7
RD[00000004] = 40A48533
RD[00000008] = 03056593
RD[0000000C] = 001A0513
RD[00000010] = 014A8633
RD[00000014] = 00B60023
RD[00000018] = FC9B62E3
RD[0000001C] = 06400493
RD[00000020] = 014A8533
RD[00000024] = 00054503
RD[00000028] = FFFFE097
RD[0000002C] = 608080E7
RD[00000030] = 001A0513
RD[00000034] = FFFA0A13
RD[00000038] = FEABC4E3
RD[0000003C] = E05FF06F
WR[00000000] = 060080E7
WR[00000004] = 40A48533
WR[00000008] = 03056593
WR[0000000C] = 001A0513
WR[00000010] = 014A8633
WR[00000014] = 00B60023
WR[00000018] = FC9B62E3
WR[0000001C] = 06400493
WR[00000020] = 014A8533
WR[00000024] = 00054503
WR[00000028] = FFFFE097
WR[0000002C] = 608080E7
WR[00000030] = 001A0513
WR[00000034] = FFFA0A13
WR[00000038] = FEABC4E3
WR[0000003C] = E05FF06F
RD[00000000] = 004A1513
RD[00000004] = 01C55513
RD[00000008] = 00AB0533
RD[0000000C] = 00054503
RD[00000010] = FFFFE097
RD[00000014] = 420080E7
RD[00000018] = 008A1513
RD[0000001C] = 01C55513
RD[00000020] = 00AB0533
RD[00000024] = 00054503
RD[00000028] = FFFFE097
RD[0000002C] = 408080E7
RD[00000030] = 00CA1513
RD[00000034] = 01C55513
RD[00000038] = 00AB0533
RD[0000003C] = 00054503
WR[00000000] = 004A1513
WR[00000004] = 01C55513
WR[00000008] = 00AB0533
WR[0000000C] = 00054503
WR[00000010] = FFFFE097
WR[00000014] = 420080E7
WR[00000018] = 008A1513
WR[0000001C] = 01C55513
WR[00000020] = 00AB0533
WR[00000024] = 00054503
WR[00000028] = FFFFE097
WR[0000002C] = 408080E7
WR[00000030] = 00CA1513
WR[00000034] = 01C55513
WR[00000038] = 00AB0533
WR[0000003C] = 00054503
RD[00000000] = 00900713
RD[00000004] = 02000793
RD[00000008] = 00C0006F
RD[0000000C] = FFF6C603
RD[00000010] = 00168693
RD[00000014] = 0FF67813
RD[00000018] = FEE80AE3
RD[0000001C] = FEF808E3
RD[00000020] = 03000713
RD[00000024] = 08E81A63
RD[00000028] = FFF6C603
RD[0000002C] = 02066613
RD[00000030] = 07800713
RD[00000034] = 0CE61263
RD[00000038] = 0006C603
RD[0000003C] = 0FF67713
WR[00000000] = 00900713
WR[00000004] = 02000793
WR[00000008] = 00C0006F
WR[0000000C] = FFF6C603
WR[00000010] = 00168693
WR[00000014] = 0FF67813
WR[00000018] = FEE80AE3
WR[0000001C] = FEF808E3
WR[00000020] = 03000713
WR[00000024] = 08E81A63
WR[00000028] = FFF6C603
WR[0000002C] = 02066613
WR[00000030] = 07800713
WR[00000034] = 0CE61263
WR[00000038] = 0006C603
WR[0000003C] = 0FF67713
RD[00000000] = 00001637
RD[00000004] = 00040513
RD[00000008] = 00060593
RD[0000000C] = 00040613
RD[00000010] = 00C12083
RD[00000014] = 00812403
RD[00000018] = 01010113
RD[0000001C] = 00000317
RD[00000020] = B3830067
RD[00000024] = F9010113
RD[00000028] = 06112623
RD[0000002C] = 06812423
RD[00000030] = 06912223
RD[00000034] = 07212023
RD[00000038] = 05312E23
RD[0000003C] = 05412C23
WR[00000000] = 00001637
WR[00000004] = 00040513
WR[00000008] = 00060593
WR[0000000C] = 00040613
WR[00000010] = 00C12083
WR[00000014] = 00812403
WR[00000018] = 01010113
WR[0000001C] = 00000317
WR[00000020] = B3830067
WR[00000024] = F9010113
WR[00000028] = 06112623
WR[0000002C] = 06812423
WR[00000030] = 06912223
WR[00000034] = 07212023
WR[00000038] = 05312E23
WR[0000003C] = 05412C23
  loaded sector 00000010 / 00000024
RD[00000000] = 02412503
RD[00000004] = 00AD9E63
RD[00000008] = 00900513
RD[0000000C] = 7C051073
RD[00000010] = 00800513
RD[00000014] = 7C051073
RD[00000018] = 7C802573
RD[0000001C] = 0240006F
RD[00000020] = 00000513
RD[00000024] = 00100593
RD[00000028] = 7C059073
RD[0000002C] = 7C051073
RD[00000030] = 7C802573
RD[00000034] = 00C0006F
RD[00000038] = 00000013
RD[0000003C] = 7C802573
WR[00000000] = 02412503
WR[00000004] = 00AD9E63
WR[00000008] = 00900513
WR[0000000C] = 7C051073
WR[00000010] = 00800513
WR[00000014] = 7C051073
WR[00000018] = 7C802573
WR[0000001C] = 0240006F
WR[00000020] = 00000513
WR[00000024] = 00100593
WR[00000028] = 7C059073
WR[0000002C] = 7C051073
WR[00000030] = 7C802573
WR[00000034] = 00C0006F
WR[00000038] = 00000013
WR[0000003C] = 7C802573
RD[00000000] = 01650793
RD[00000004] = 00F58323
RD[00000008] = 00E60323
RD[0000000C] = 00350513
RD[00000010] = 00C58593
RD[00000014] = 00C60613
RD[00000018] = F4D518E3
RD[0000001C] = 00235537
RD[00000020] = 7B450913
RD[00000024] = 00200593
RD[00000028] = 00B90DA3
RD[0000002C] = 02090FA3
RD[00000030] = 00300593
RD[00000034] = 7AB50A23
RD[00000038] = 0C040C63
RD[0000003C] = 00000493
WR[00000000] = 01650793
WR[00000004] = 00F58323
WR[00000008] = 00E60323
WR[0000000C] = 00350513
WR[00000010] = 00C58593
WR[00000014] = 00C60613
WR[00000018] = F4D518E3
WR[0000001C] = 00235537
WR[00000020] = 7B450913
WR[00000024] = 00200593
WR[00000028] = 00B90DA3
WR[0000002C] = 02090FA3
WR[00000030] = 00300593
WR[00000034] = 7AB50A23
WR[00000038] = 0C040C63
WR[0000003C] = 00000493
RD[00000000] = 84458593
RD[00000004] = 00236637
RD[00000008] = 8D460693
RD[0000000C] = 00040613
RD[00000010] = 00000097
RD[00000014] = A14080E7
RD[00000018] = 00203537
RD[0000001C] = 29550513
RD[00000020] = FFFFF097
RD[00000024] = 190080E7
RD[00000028] = 00A00513
RD[0000002C] = 01C12083
RD[00000030] = 01812403
RD[00000034] = 01412483
RD[00000038] = 01012903
RD[0000003C] = 00C12983
WR[00000000] = 84458593
WR[00000004] = 00236637
WR[00000008] = 8D460693
WR[0000000C] = 00040613
WR[00000010] = 00000097
WR[00000014] = A14080E7
WR[00000018] = 00203537
WR[0000001C] = 29550513
WR[00000020] = FFFFF097
WR[00000024] = 190080E7
WR[00000028] = 00A00513
WR[0000002C] = 01C12083
WR[00000030] = 01812403
WR[00000034] = 01412483
WR[00000038] = 01012903
WR[0000003C] = 00C12983
RD[00000000] = 00000013
RD[00000004] = 00000013
RD[00000008] = 00000013
RD[0000000C] = 00000013
RD[00000010] = 00000013
RD[00000014] = 00000013
RD[00000018] = 00000013
RD[0000001C] = 00000013
RD[00000020] = 00000013
RD[00000024] = 00000013
RD[00000028] = 00000013
RD[0000002C] = 00000013
RD[00000030] = 00000013
RD[00000034] = 00000013
RD[00000038] = 00000013
RD[0000003C] = 00000013
WR[00000000] = 00000013
WR[00000004] = 00000013
WR[00000008] = 00000013
WR[0000000C] = 00000013
WR[00000010] = 00000013
WR[00000014] = 00000013
WR[00000018] = 00000013
WR[0000001C] = 00000013
WR[00000020] = 00000013
WR[00000024] = 00000013
WR[00000028] = 00000013
WR[0000002C] = 00000013
WR[00000030] = 00000013
WR[00000034] = 00000013
WR[00000038] = 00000013
WR[0000003C] = 00000013
RD[00000000] = 614080E7
RD[00000004] = FA9FF06F
RD[00000008] = 23C12083
RD[0000000C] = 23812403
RD[00000010] = 23412483
RD[00000014] = 23012903
RD[00000018] = 22C12983
RD[0000001C] = 22812A03
RD[00000020] = 22412A83
RD[00000024] = 22012B03
RD[00000028] = 21C12B83
RD[0000002C] = 21812C03
RD[00000030] = 21412C83
RD[00000034] = 21012D03
RD[00000038] = 20C12D83
RD[0000003C] = 24010113
WR[00000000] = 614080E7
WR[00000004] = FA9FF06F
WR[00000008] = 23C12083
WR[0000000C] = 23812403
WR[00000010] = 23412483
WR[00000014] = 23012903
WR[00000018] = 22C12983
WR[0000001C] = 22812A03
WR[00000020] = 22412A83
WR[00000024] = 22012B03
WR[00000028] = 21C12B83
WR[0000002C] = 21812C03
WR[00000030] = 21412C83
WR[00000034] = 21012D03
WR[00000038] = 20C12D83
WR[0000003C] = 24010113
RD[00000000] = 00008067
RD[00000004] = 00000000
RD[00000008] = 00200F40
RD[0000000C] = 0020104C
RD[00000010] = 00200F94
RD[00000014] = 00201084
RD[00000018] = 002010BC
RD[0000001C] = 00201024
RD[00000020] = 00201024
RD[00000024] = 00201138
RD[00000028] = 00201024
RD[0000002C] = 00200F5C
RD[00000030] = 002030E8
RD[00000034] = 00202CD9
RD[00000038] = 202D2D2D
RD[0000003C] = 61657263
WR[00000000] = 00008067
WR[00000004] = 00000000
WR[00000008] = 00200F40
WR[0000000C] = 0020104C
WR[00000010] = 00200F94
WR[00000014] = 00201084
WR[00000018] = 002010BC
WR[0000001C] = 00201024
WR[00000020] = 00201024
WR[00000024] = 00201138
WR[00000028] = 00201024
WR[0000002C] = 00200F5C
WR[00000030] = 002030E8
WR[00000034] = 00202CD9
WR[00000038] = 202D2D2D
WR[0000003C] = 61657263
RD[00000000] = 2E747261
RD[00000004] = 2D2D2D20
RD[00000008] = 43000A2D
RD[0000000C] = 4F204352
RD[00000010] = 7228204B
RD[00000014] = 79727465
RD[00000018] = 2964253D
RD[0000001C] = 2D2D000A
RD[00000020] = 53202D2D
RD[00000024] = 6F632041
RD[00000028] = 64206572
RD[0000002C] = 20617461
RD[00000030] = 61206277
RD[00000034] = 65726464
RD[00000038] = 6D207373
RD[0000003C] = 73207061
WR[00000000] = 2E747261
WR[00000004] = 2D2D2D20
WR[00000008] = 43000A2D
WR[0000000C] = 4F204352
WR[00000010] = 7228204B
WR[00000014] = 79727465
WR[00000018] = 2964253D
WR[0000001C] = 2D2D000A
WR[00000020] = 53202D2D
WR[00000024] = 6F632041
WR[00000028] = 64206572
WR[0000002C] = 20617461
WR[00000030] = 61206277
WR[00000034] = 65726464
WR[00000038] = 6D207373
WR[0000003C] = 73207061
RD[00000000] = 7C0A726F
RD[00000004] = 52415520
RD[00000008] = 3A202054
RD[0000000C] = 494D4D20
RD[00000010] = 6F63204F
RD[00000014] = 6C6F736E
RD[00000018] = 207C0A65
RD[0000001C] = 20444D43
RD[00000020] = 203A2020
RD[00000024] = 6C6C6568
RD[00000028] = 70202C6F
RD[0000002C] = 656D6972
RD[00000030] = 64202C73
RD[00000034] = 2C706D75
RD[00000038] = 5F617320
RD[0000003C] = 72617473
WR[00000000] = 7C0A726F
WR[00000004] = 52415520
WR[00000008] = 3A202054
WR[0000000C] = 494D4D20
WR[00000010] = 6F63204F
WR[00000014] = 6C6F736E
WR[00000018] = 207C0A65
WR[0000001C] = 20444D43
WR[00000020] = 203A2020
WR[00000024] = 6C6C6568
WR[00000028] = 70202C6F
WR[0000002C] = 656D6972
WR[00000030] = 64202C73
WR[00000034] = 2C706D75
WR[00000038] = 5F617320
WR[0000003C] = 72617473
  loaded sector 00000018 / 00000024
RD[00000000] = 72702065
RD[00000004] = 7365636F
RD[00000008] = 50000A73
RD[0000000C] = 43494E41
RD[00000010] = 7325203A
RD[00000014] = 3A64253A
RD[00000018] = 20435020
RD[0000001C] = 6173696D
RD[00000020] = 6E67696C
RD[00000024] = 73206465
RD[00000028] = 3D637065
RD[0000002C] = 73207825
RD[00000030] = 6C617674
RD[00000034] = 2078253D
RD[00000038] = 61747373
RD[0000003C] = 3D737574
WR[00000000] = 72702065
WR[00000004] = 7365636F
WR[00000008] = 50000A73
WR[0000000C] = 43494E41
WR[00000010] = 7325203A
WR[00000014] = 3A64253A
WR[00000018] = 20435020
WR[0000001C] = 6173696D
WR[00000020] = 6E67696C
WR[00000024] = 73206465
WR[00000028] = 3D637065
WR[0000002C] = 73207825
WR[00000030] = 6C617674
WR[00000034] = 2078253D
WR[00000038] = 61747373
WR[0000003C] = 3D737574
RD[00000000] = 13004015
RD[00000004] = 232AF505
RD[00000008] = 3702A12E
RD[0000000C] = 13004015
RD[00000010] = 2332D505
RD[00000014] = 3704A122
RD[00000018] = 13004015
RD[0000001C] = 232C8505
RD[00000020] = 3704A120
RD[00000024] = 13000185
RD[00000028] = 236A0505
RD[0000002C] = 3702A126
RD[00000030] = 13004015
RD[00000034] = 23360505
RD[00000038] = 3700A12C
RD[0000003C] = 13004015
WR[00000000] = 13004015
WR[00000004] = 232AF505
WR[00000008] = 3702A12E
WR[0000000C] = 13004015
WR[00000010] = 2332D505
WR[00000014] = 3704A122
WR[00000018] = 13004015
WR[0000001C] = 232C8505
WR[00000020] = 3704A120
WR[00000024] = 13000185
WR[00000028] = 236A0505
WR[0000002C] = 3702A126
WR[00000030] = 13004015
WR[00000034] = 23360505
WR[00000038] = 3700A12C
WR[0000003C] = 13004015
RD[00000000] = 13920080
RD[00000004] = 97020005
RD[00000008] = E7000010
RD[0000000C] = 13914080
RD[00000010] = 13008005
RD[00000014] = 970FF575
RD[00000018] = E7000010
RD[0000001C] = 6F904080
RD[00000020] = 13F91FF0
RD[00000024] = 9700A005
RD[00000028] = E7000010
RD[0000002C] = 338F4080
RD[00000030] = 23009C05
RD[00000034] = E3000500
RD[00000038] = 13E8048E
RD[0000003C] = 6F06C105
WR[00000000] = 13920080
WR[00000004] = 97020005
WR[00000008] = E7000010
WR[0000000C] = 13914080
WR[00000010] = 13008005
WR[00000014] = 970FF575
WR[00000018] = E7000010
WR[0000001C] = 6F904080
WR[00000020] = 13F91FF0
WR[00000024] = 9700A005
WR[00000028] = E7000010
WR[0000002C] = 338F4080
WR[00000030] = 23009C05
WR[00000034] = E3000500
WR[00000038] = 13E8048E
WR[0000003C] = 6F06C105
RD[00000000] = E7000000
RD[00000004] = 6F7D0080
RD[00000008] = 63CCDFF0
RD[0000000C] = 03000A8A
RD[00000010] = 97050125
RD[00000014] = E7000010
RD[00000018] = 63AC4080
RD[0000001C] = 1309A516
RD[00000020] = 9700C005
RD[00000024] = E7000000
RD[00000028] = 13378080
RD[0000002C] = 6F04C10A
RD[00000030] = 37CA5FF0
RD[00000034] = 13002005
RD[00000038] = 9704C10A
RD[0000003C] = E7000000
WR[00000000] = E7000000
WR[00000004] = 6F7D0080
WR[00000008] = 63CCDFF0
WR[0000000C] = 03000A8A
WR[00000010] = 97050125
WR[00000014] = E7000010
WR[00000018] = 63AC4080
WR[0000001C] = 1309A516
WR[00000020] = 9700C005
WR[00000024] = E7000000
WR[00000028] = 13378080
WR[0000002C] = 6F04C10A
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
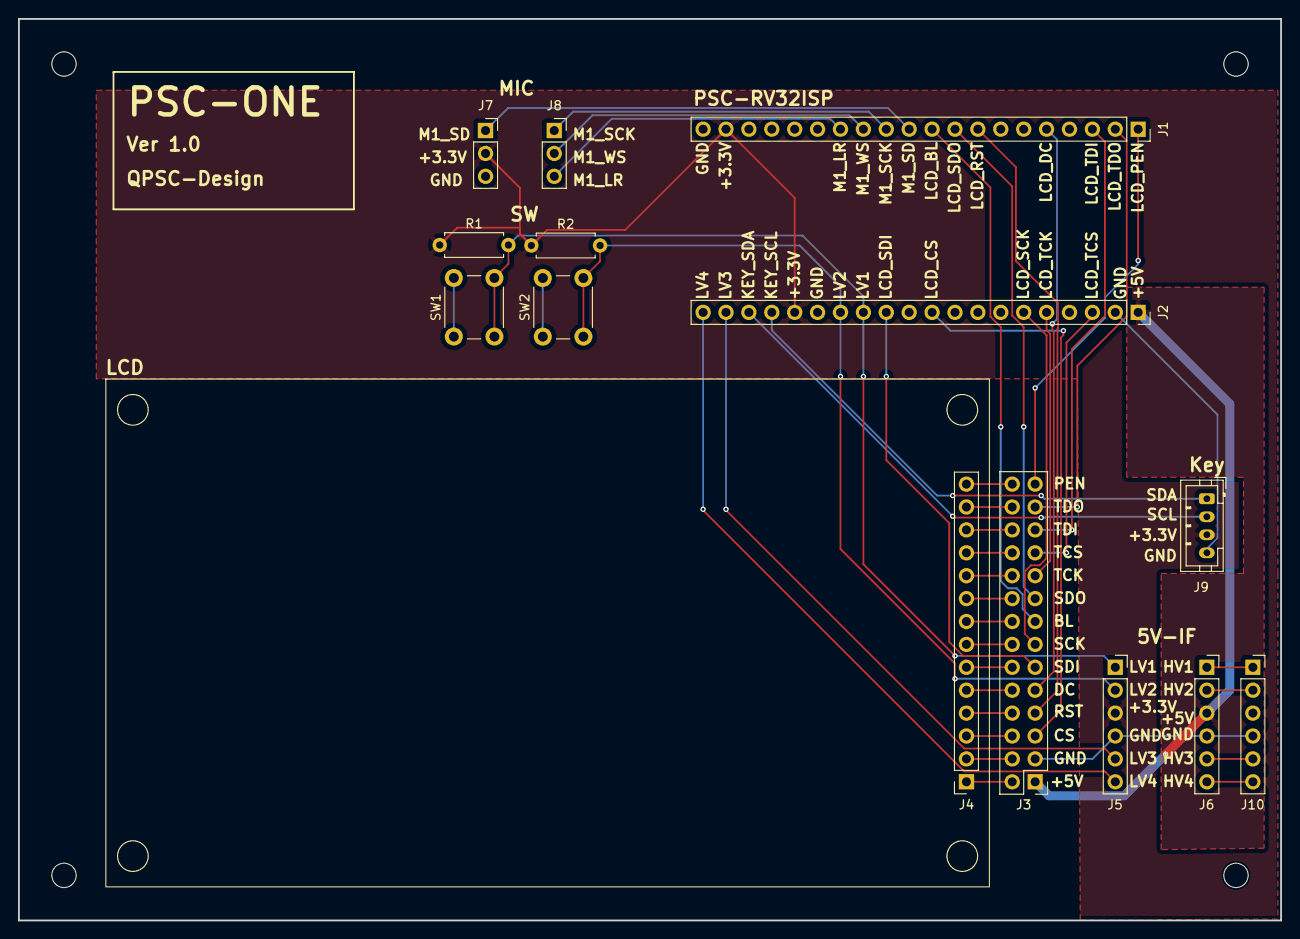
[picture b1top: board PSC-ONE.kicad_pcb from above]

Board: 2 copper layers, 140.0 x 100.0 mm, 14 parts (0 on the bottom side), 43 nets.

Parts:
J1, J2: FPGA_Conn_01x20_Socket; PinSocket_1x20_P2.54mm_Vertical
J3: 2.54mmピッチピンヘッダー 2x14; PinHeader_2x14_P2.54mm_Vertical_2
J4: 2.54mmピッチピンソケット 1x14; LCD_PinSocket_1x14_P2.54mm_Vertical
J5, J6: 2.54mmピッチピンソケット 1x6; PinSocket_1x06_P2.54mm_Vertical
J7, J8: 2.54mmピッチピンソケットx3pin; PinSocket_1x03_P2.54mm_Vertical
J9: Grove Female Header DIP-4P; JST_PH_B4B-PH-K_1x04_P2.00mm_Vertical
J10: Conn_01x06_Pin; PinSocket_1x06_P2.54mm_Vertical
R1, R2: 1k; R_Axial_DIN0207_L6.3mm_D2.5mm_P7.62mm_Horizontal
SW1, SW2: SW_Push; SW_PUSH_6mm

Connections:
/HV1: J6.1, J10.1
/HV2: J6.2, J10.2
/HV3: J6.5, J10.5
/HV4: J6.6, J10.6
/KEY_SCL: J2.17, J9.1
/KEY_SDA: J2.18, J9.2
/LCD_BL: J1.10, J3.8
/LCD_CS: J2.10, J3.3
/LCD_DC: J1.5, J3.5
/LCD_PEN: J1.1, J3.14
/LCD_RST: J1.8, J3.4
/LCD_SCK: J2.6, J3.7
/LCD_SDI: J2.12, J3.6
/LCD_SDO: J1.9, J3.9
/LCD_TCK: J2.5, J3.10
/LCD_TCS: J2.3, J3.11
/LCD_TDI: J1.3, J3.12
/LCD_TDO: J1.2, J3.13
/LV1: J2.13, J5.1, R1.2, SW1.2
/LV2: J2.14, J5.2, R2.2, SW2.2
/LV3: J2.19, J5.5
/LV4: J2.20, J5.6
/M1_LR: J1.14, J8.3
/M1_SCK: J1.12, J8.1
/M1_SD: J1.11, J7.1
/M1_WS: J1.13, J8.2
GND: J1.20, J2.2, J2.15, J3.2, J5.4, J6.4, J7.3, J9.4, J10.4, SW1.1, SW2.1
unnamed: J3.15, J4.1
unnamed: J3.16, J4.2
unnamed: J3.17, J4.3
unnamed: J3.18, J4.4
unnamed: J3.19, J4.5
unnamed: J3.20, J4.6
unnamed: J3.21, J4.7
unnamed: J3.22, J4.8
unnamed: J3.23, J4.9
unnamed: J3.24, J4.10
unnamed: J3.25, J4.11
unnamed: J3.26, J4.12
unnamed: J3.27, J4.13
unnamed: J3.28, J4.14
VDD+3V3: J1.19, J2.16, J5.3, J7.2, J9.3, R1.1, R2.1
VDD+5V: J2.1, J3.1, J6.3

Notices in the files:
board/PSC-ONE/README.md:
Hardware design files, schematics, PCB layouts, and related documentation are licensed under CERN-OHL-S v2.
Copyright (c) 2026 QPSC-Design
